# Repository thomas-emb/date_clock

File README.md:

# Date clock

This date clock aims to modify an existing analog quartz wall clock to render the date with its hands.

As clocks have three hands, a date clock allows for the rendering of three date properties:

* `hours` now displays the current month.
* `minutes` now displays the current day of the month.
* `seconds` now displays the current day of the week.

As weeks tend to start on either Sunday or Monday, dependent on the country,
this date clock uses day 0-6, where the meaning is entirely dependent on the face plate.

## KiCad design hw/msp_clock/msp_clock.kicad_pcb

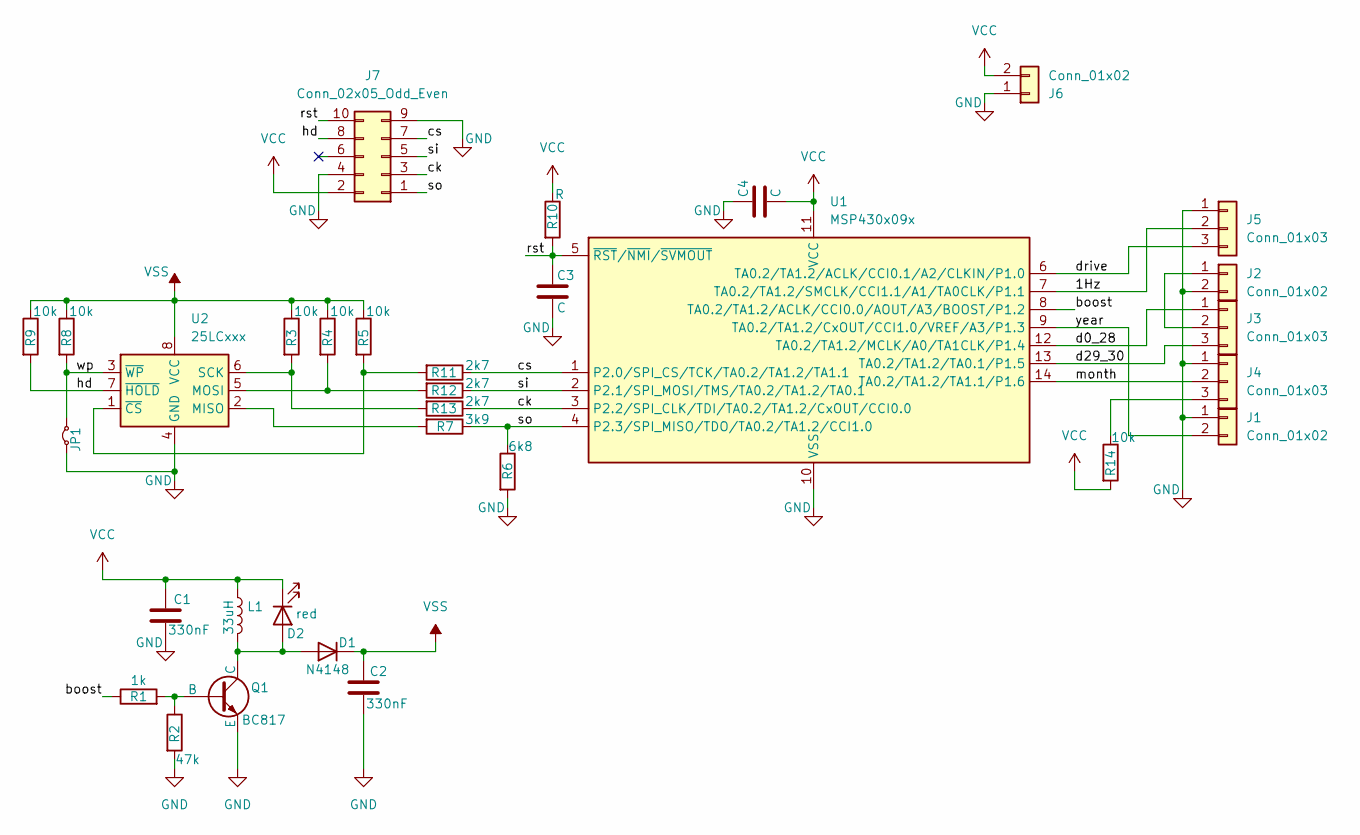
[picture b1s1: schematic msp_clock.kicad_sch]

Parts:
C1, C2: 330nF; C_0603_1608Metric_Pad1.08x0.95mm_HandSolder
C3, C4: C; C_0603_1608Metric_Pad1.08x0.95mm_HandSolder
D1: N4148; D_0603_1608Metric_Pad1.05x0.95mm_HandSolder
D2: red; LED_0603_1608Metric_Pad1.05x0.95mm_HandSolder
J1, J2, J6: Conn_01x02; PinHeader_1x02_P1.27mm_Vertical
J3, J4, J5: Conn_01x03; PinHeader_1x03_P1.27mm_Vertical
J7: Conn_02x05_Odd_Even; PinHeader_2x05_P1.27mm_Vertical
JP1: Jumper_2_Small_Bridged; R_0603_1608Metric_Pad0.98x0.95mm_HandSolder
L1: 33uH; L_Murata_LQH2MCNxxxx02_2.0x1.6mm
Q1: BC817; SOT-23-3
R1: 1k; R_0603_1608Metric_Pad0.98x0.95mm_HandSolder
R2: 47k; R_0603_1608Metric_Pad0.98x0.95mm_HandSolder
R3, R4, R5, R8, R9, R14: 10k; R_0603_1608Metric_Pad0.98x0.95mm_HandSolder
R6: 6k8; R_0603_1608Metric_Pad0.98x0.95mm_HandSolder
R7: 3k9; R_0603_1608Metric_Pad0.98x0.95mm_HandSolder
R10: R; R_0603_1608Metric_Pad0.98x0.95mm_HandSolder
R11, R12, R13: 2k7; R_0603_1608Metric_Pad0.98x0.95mm_HandSolder
U1: MSP430x09x; TSSOP-14_4.4x5mm_P0.65mm
U2: 25LCxxx; SOIC-8_3.9x4.9mm_P1.27mm

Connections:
/1Hz: J5.2, U1.7 (TA0.2/TA1.2/SMCLK/CCI1.1/A1/TA0CLK/P1.1)
/boost: R1.1, U1.8 (TA0.2/TA1.2/ACLK/CCI0.0/AOUT/A3/BOOST/P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)
/ck: J7.3, R13.1, U1.3 (P2.2/SPI_CLK/TDI/TA0.2/TA1.2/CxOUT/CCI0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)
/cs: J7.7, R11.1, U1.1 (P2.0/SPI_CS/TCK/TA0.2/TA1.2/TA1.1)
/d0_28: J3.1, U1.12 (TA0.2/TA1.2/MCLK/A0/TA1CLK/P1.4)
/d29_30: J3.3, U1.13 (TA0.2/TA1.2/TA0.1/P1.5)
/drive: J5.3, U1.6 (TA0.2/TA1.2/ACLK/CCI0.1/A2/CLKIN/P1.0)
/hd: J7.8, R9.2, U2.7 (~HOLD)
/month: J4.2, U1.14 (TA0.2/TA1.2/TA1.1/P1.6)
/rst: C3.1, J7.10, R10.2, U1.5 (~RST/~NMI/~SVMOUT)
/si: J7.5, R12.1, U1.2 (P2.1/SPI_MOSI/TMS/TA0.2/TA1.2/TA0.1)
/so: J7.1, R6.1, R7.1, U1.4 (P2.3/SPI_MISO/TDO/TA0.2/TA1.2/CCI1.0)
/wp: JP1.2 (B), R8.2, U2.3 (~WP)
/year: J1.2, U1.9 (TA0.2/TA1.2/CxOUT/CCI1.0/VREF/A3/P1.3)
GND: C1.2, C2.2, C3.2, C4.1, J1.1, J2.2, J4.1, J5.1, J6.1, J7.4, J7.9, JP1.1 (A), Q1.3 (E), R2.2, R6.2, U1.10 (VSS), U2.4 (GND)
unnamed: D1.2 (A), D2.2 (A), L1.2, Q1.1 (C)
unnamed: J2.1, J3.2
unnamed: J4.3, R14.1
unnamed: Q1.2 (B), R1.2, R2.1
unnamed: R7.2, U2.2 (MISO)
unnamed: R4.2, R12.2, U2.5 (MOSI)
unnamed: R3.2, R13.2, U2.6 (SCK)
unnamed: R5.2, R11.2, U2.1 (~CS)
VCC: C1.1, C4.2, D2.1 (K), J6.2, J7.2, L1.1, R10.1, R14.2, U1.11 (VCC)
VSS: C2.1, D1.1 (K), R3.1, R4.1, R5.1, R8.1, R9.1, U2.8 (VCC)

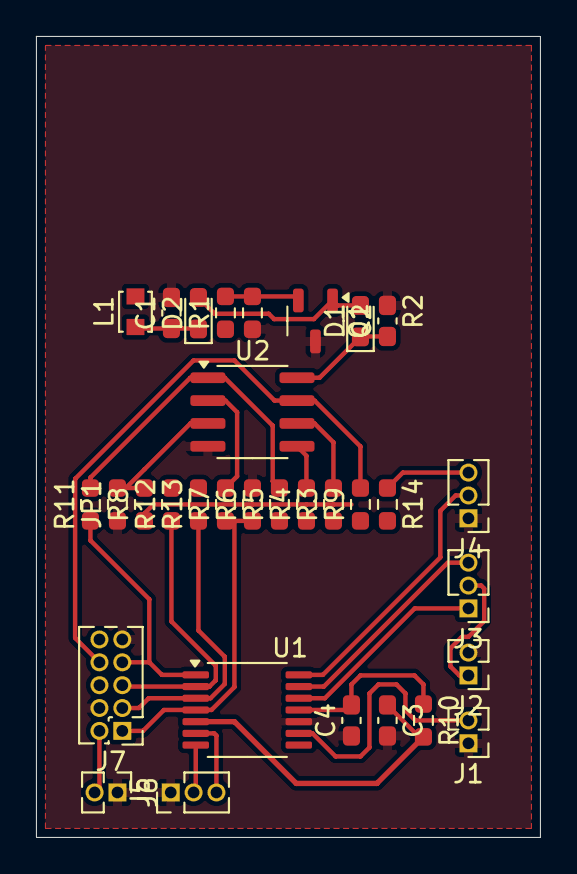
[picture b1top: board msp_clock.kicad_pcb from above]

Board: 2 copper layers, 28.0 x 44.5 mm, 32 parts (0 on the bottom side), 25 nets.

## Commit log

2024-09-27 building tests for the clock-simulator
2024-10-04 tests added for simulator and pin logic
2024-10-04 Add simulator constructor tests
2024-10-08 implement some happy flows for the clock, add simulator hour hand behaviour
2024-10-09 improve test output
2024-10-10 initial kicad_mod footprint generator
2024-10-11 fully parametrized generation of encoders
2024-10-12 added tests (failing right now) for embedded code
2024-10-12 GitHub templates
2024-10-12 added hardware designs
2024-10-12 move encoder wheel generator to `hw/encoders`
2024-10-12 calculate *actual* spacing for encoders, and some refactoring
2024-10-14 refactoring of encoders, updated PCB stackup, added face plates
2024-10-16 Run C++ tests in GitHub workflow
2024-10-16 Fix sloppy C code to compile in action
2024-10-17 Add regression testing for generated encoders
2024-10-17 update python action to v5
2024-10-17 change working directory for encoder test
2024-10-17 clean up rendering of coordinates in kicad_mod
